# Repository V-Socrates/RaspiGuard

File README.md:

# RaspiGuard
Vivek Socrates
Karel Tutsu
Heakeme Williams

# RASPIGUARD Board For Home Monitoring Build Instrutions

### Project website
Click [here](http://raspiguard.club) to get directed

### Background Knowledge
RaspiGuard is a home security/surveillance system that is used to monitor a room remotely using our android application. The current operational functionality is door and moisture sensors. We are currently working on the functionality of light sensors as well as various other sensors. Installing a home security system can be costly, but needing one and not having one can cost you more. Fortunately, you will not have that dilemma with RaspiGuard. RaspiGuard is a cost-effective and easy to install security system that you can easily setup and deploy on your own.

### Materials\Components Needed
Click [Here](https://www.adafruit.com/) To Buy Parts

Components	   |                                Cost
------------ |  ---------------------------------------
 Raspberry Pi 3 Model B	 |                     $48.98
 Raspberry Pi Power Adapter	|                  $16.95
 ADATA Premier 8GB microSDHC UHS-I Class 10	|  $8.99
ADATA microReader Ver.3 microSDHC	          |  $4.99
adafruit PiTFT Plus 480x320 3.5"	          |  $44.95
adafruit ADS1115	                          |  $14.95
SparkFun Soil Moisture Sensor	              |  $5.95
 Photo Cell (CdS Photoresistor)	            |  $0.95
 Magnetic Contact Switchs	                  |  $3.95
 Piezo Buzzer - PS1240	                      |  $1.50
 GPIO 2x13pin Ribbon Cable	                  |  $2.95
 Male To Male 2x13pin Header	                |  $1.75
 Jumper Wire Cables	                        |  $1.95
Raspbian Stretch with Desktop (OS)	        |  $0.00
TAX	                                        | $20.65
TOTAL	                                      | $179.46

### Boards Needed

Designing the boards can be quite an annoying process, however, We have designed these boards and they are available for download if needed.
* To download the RaspiGuard board file in Eagle, please click [HERE](https://github.com/V-Socrates/RaspiGuard/blob/master/Hardware/RaspiGuardProtoBoard.zip)

* To download the RaspiGuard Schematic in Fritzing, please click [HERE](https://github.com/V-Socrates/RaspiGuard/blob/master/Hardware/RaspiGuard%20Schematic.fzz)

### Components Needed For Testing

* Raspberry Pi
* Keyboard
* Monitor

### Implementing Everything Together / Testing.

1.	Build the above circuit using the GPIO pinout found on the PiTFT. The picture above shows a Raspberry Pi Model B which the pinout mirrors. It is recommended to use a ribbon cable to connect the above circuit for testing and easy modifications.
2.	Place the PiTFT on to the your Raspberry Pi 3 B.
3.	Download the Jesse Pitft image from adafruit (https://s3.amazonaws.com/adafruit-raspberry-pi/2016-11-08-pitft-35r.zip) and flash the image onto you microSD card. Minimum 8GB.
4.	Insert your SD card into your Raspberry Pi 3 B and power on your Pi.
5.	After powering on connect to the internet via Ethernet cable or Wifi.
6.	Execute the commands below into a terminal window. Default sudo password is raspberry.
* cd ~
* sudo apt-get update
* sudo apt-get install build-essential python-dev python-smbus git
* cd ~
* git clone https://github.com/adafruit/Adafruit_Python_ADS1x15.git
* cd Adafruit_Python_ADS1x15
* sudo python setup.py install
* sudo apt-get install build-essential python-dev python-smbus python-pip python-mysqldb
* sudo pip install adafruit-ads1x15
* cd ~/Adafruit_Python_ADS1x15/examples
*wget https://raw.githubusercontent.com/V-Socrates/RaspiGuard/master/Hardware/RG.py
7.	Execute the RG.py python script using “sudo python RG.py” to start your RaspiGuard unit.

## Software Build Instruction

### RaspiGuard Website Assistance

* To see the source code of our website, please click [here](https://github.com/V-Socrates/RaspiGuard/tree/master/Software/RaspiGuardWeb).
* To see the configuration file of the website, click [here](https://github.com/V-Socrates/RaspiGuard/blob/master/Software/RaspiGuardWeb/config.php).

### RaspiGaurd Android App Assistance

* To see the source code of our Android App, please click [here](https://github.com/V-Socrates/RaspiGuard/tree/master/Software/Team.RG/RaspiGuard).
* To see the configuration file of the Android App, click [here](https://github.com/V-Socrates/RaspiGuard/blob/master/Software/Team.RG/RaspiGuard/src/main/java/Team/RG/RaspiGuard/SupportClasses/Config.java).

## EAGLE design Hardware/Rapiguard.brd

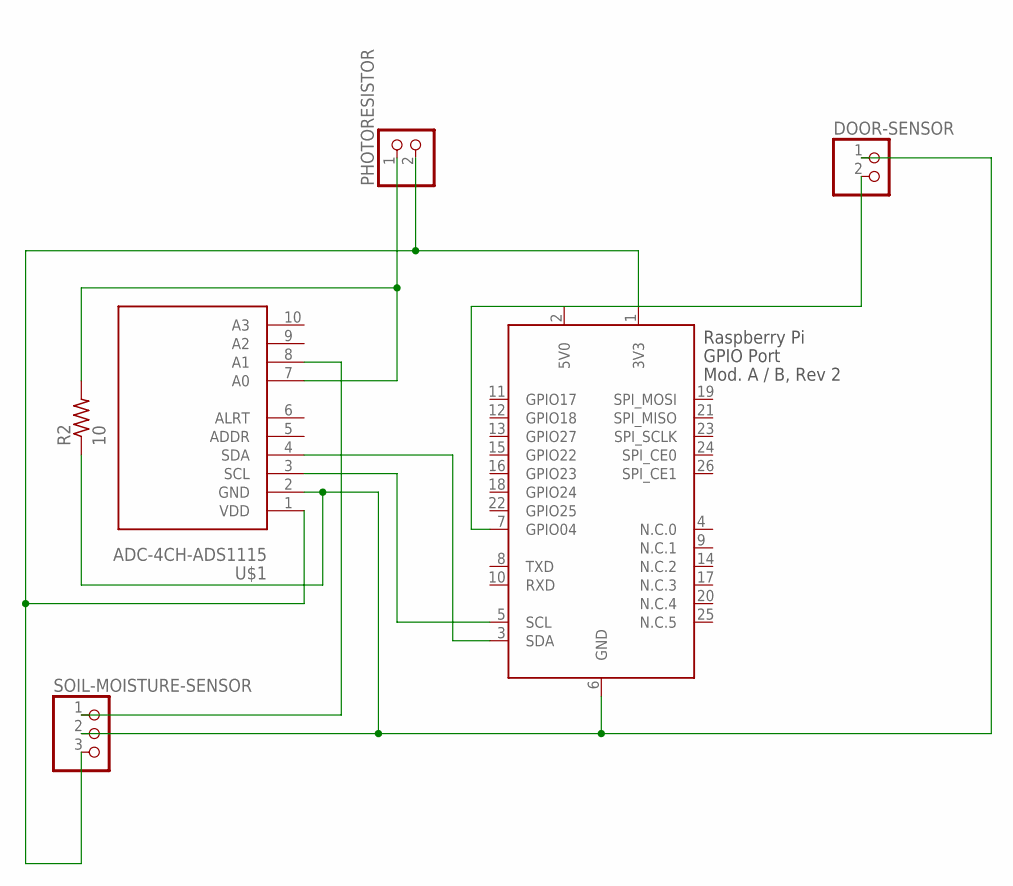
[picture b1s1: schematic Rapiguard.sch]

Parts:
DOOR-SENSOR: PINHD-1X2; 1X02
PHOTORESISTOR: PINHD-1X2; 1X02
R2: 10; 0204/7
SOIL-MOISTURE-SENSOR: PINHD-1X3; 1X03
U$1: ADC-4CH-ADS1115
X2: RASPI_BOARD_B-_E0; RASPI_BOARD_B-_EDGES_0DRILL

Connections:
5V0: X2.2 (5V0)
A0: PHOTORESISTOR.1, R2.2, U$1.7 (A0)
A1: SOIL-MOISTURE-SENSOR.1, U$1.8 (A1)
GND: DOOR-SENSOR.1, R2.1, SOIL-MOISTURE-SENSOR.2, U$1.2 (GND), X2.6 (GND)
GPIO04: DOOR-SENSOR.2, X2.7 (GPIO04)
SCL: U$1.3 (SCL), X2.5 (SCL)
SDA: U$1.4 (SDA), X2.3 (SDA)
VDD: PHOTORESISTOR.2, SOIL-MOISTURE-SENSOR.3, U$1.1 (VDD), X2.1 (3V3)

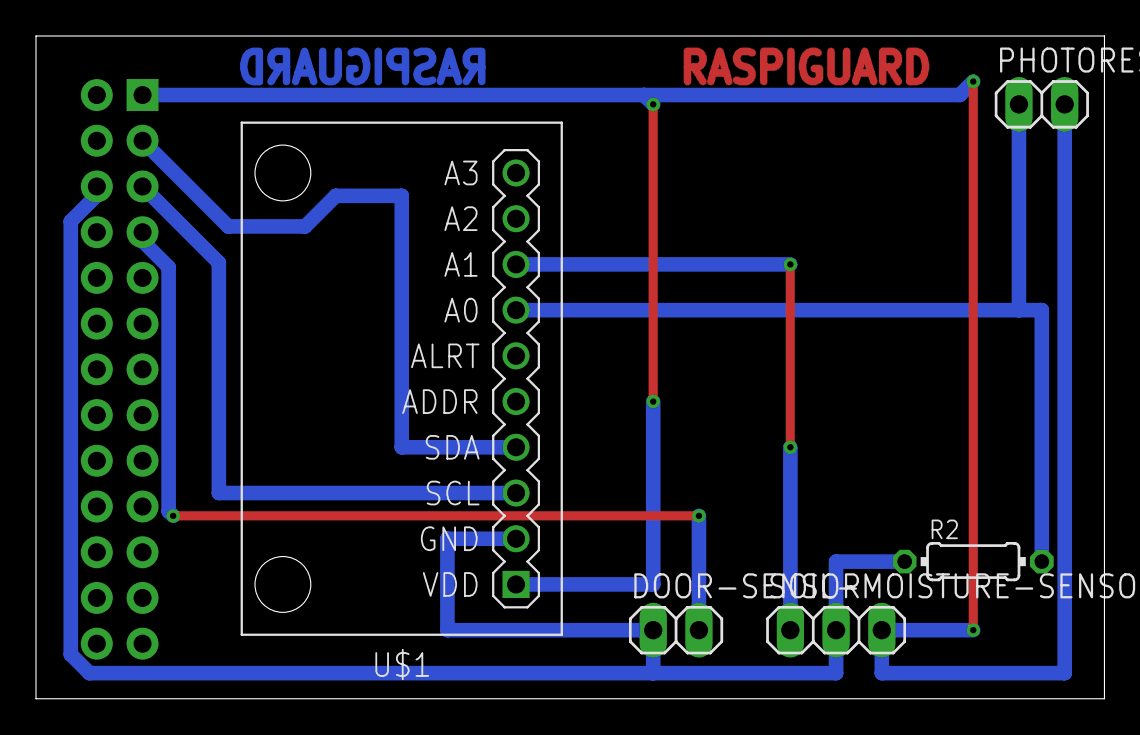
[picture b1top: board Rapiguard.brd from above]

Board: 2 copper layers, 59.4 x 36.8 mm, 6 parts (1 on the bottom side), 7 nets.

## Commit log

2018-01-31 Initial Repositiory Setup
    organizing repository
2018-01-31 null
    null
2018-01-31 null
    null
2018-02-04 Project Proposal
    -index
    -documentation (xlsx-pdf)
2018-02-05 Init
    w2 lab
2018-02-05 reference
2018-02-07 Organizing
2018-02-11 Techinical Report Template
    Techinical Report Template created and ready to be filled.
2018-02-11 SRS
    2.4.4, 2.4.5 updated
2018-02-21 PCB
    PCB
2018-02-21 1
    1
2018-02-26 PCB Update
2018-02-26 Report Update
2018-02-27 WebSkeleton
2018-03-02 js_edit1
2018-03-02 from static to dynamic
2018-03-02 icons
2018-03-03 Updated RaspiGuard Schematic
    Piezo Buzzer added
2018-03-05 Week 6 Progress Report
    Week 6 Progress Report
    Version 1
2018-03-13 Update config.php
    credentials removal
2018-03-14 Hardware Update
    RaspiGuard Script
2018-03-16 Report Formatted
2018-03-19 Add files via upload
    MySQL database login system & sessions
2018-03-23 Updates
    -From now on all the data is account specific to the logged in user (note : the data is still mocked but its tied to the user)
    -Added new area chart 'Average Daily Light Levels' on the dashboard
    -Added custom website icon
    -Added new menu item 'Unit Status' where users can view the 'live' status and measurements of their device(s)
2018-03-23 cosmetic
    -Changed color for Light Level Chart
2018-03-25 Update
    -Ability to toggle alarm on/off remotely through website
2018-03-25 Week 9 Update
    - OACETT Checklist
    - Conclusion added to TR
2018-03-27 Hardware code
2018-04-14 Completed RG Code
2018-04-16 From static dates to dynamic dates for the charts
2018-04-16 latest updates
2018-04-22 new name
2018-04-23 Final Changes

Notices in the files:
parts and their libraries:
diy-modules: Released under the Creative Commons Attribution 4.0 International License: http://creativecommons.org/licenses/by/4.0
